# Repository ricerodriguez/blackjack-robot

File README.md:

# Blackjack Robot
Source code for a robot that automates a game of blackjack for 5 players.

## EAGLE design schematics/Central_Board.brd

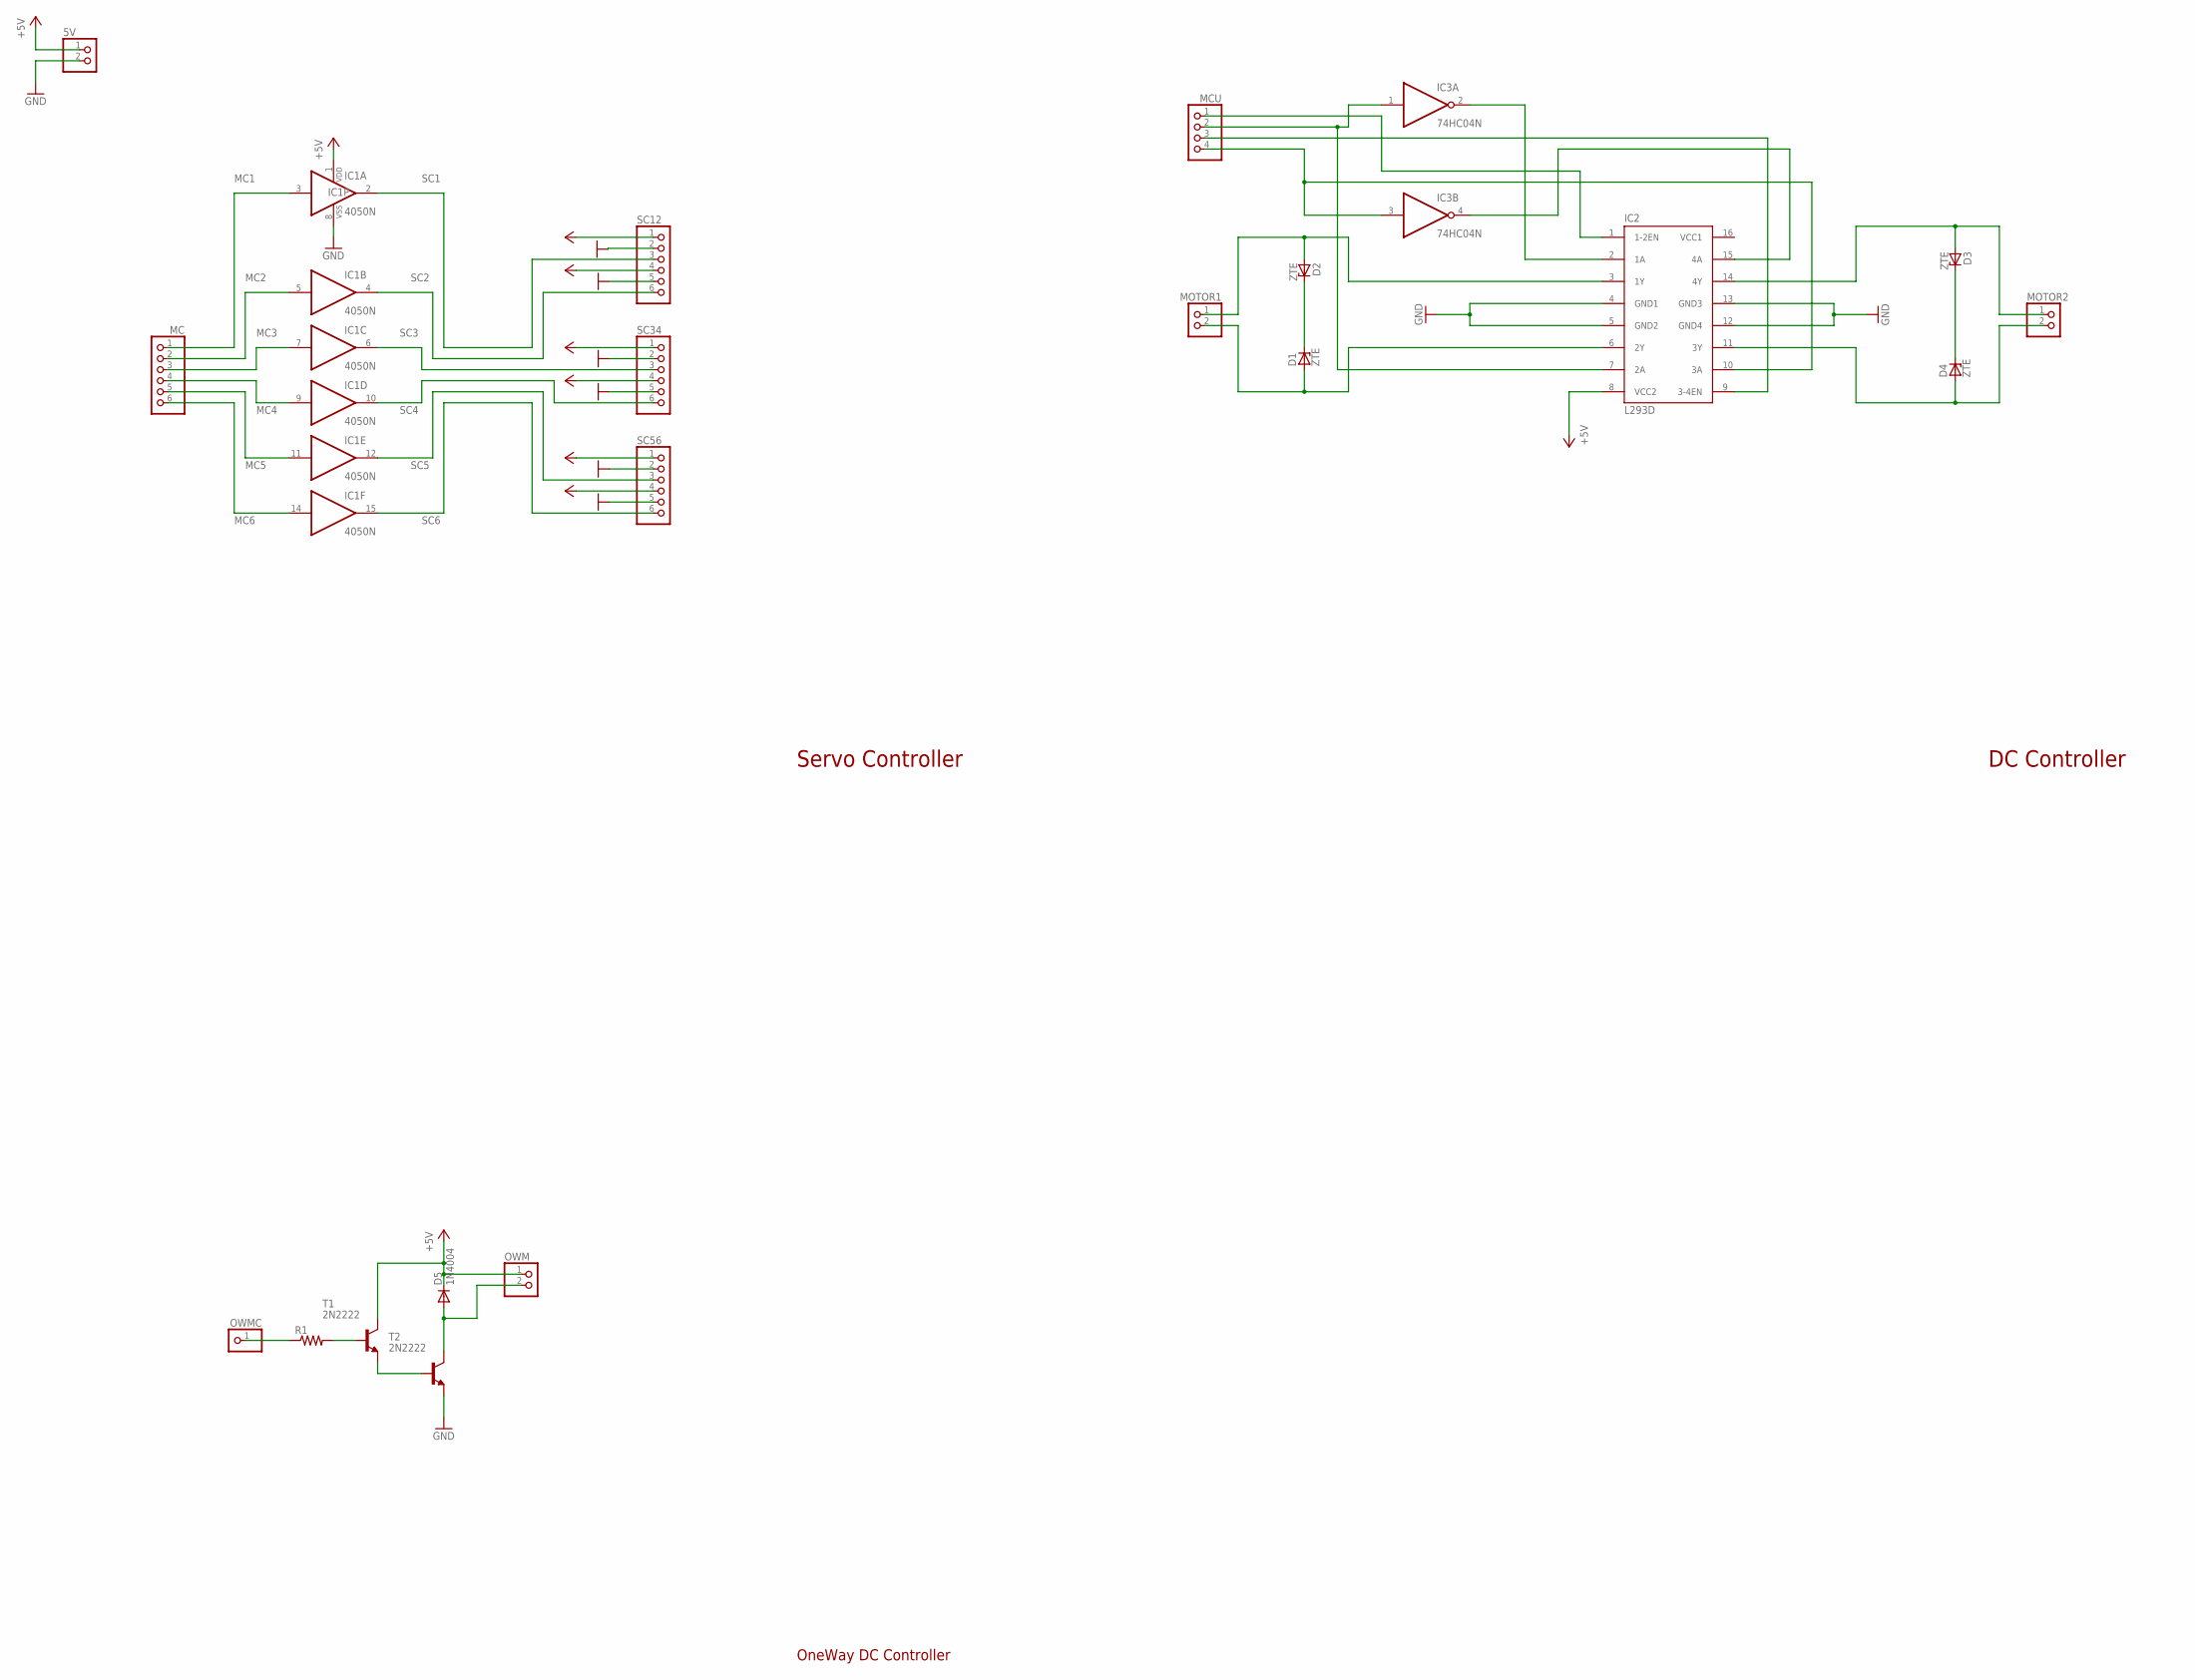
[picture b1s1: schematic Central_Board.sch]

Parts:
5V: PINHD-1X2; 1X02
D1, D2, D3, D4: ZTE; DO35Z10
D5: 1N4004; DO41-10
IC1: 4050N; DIL16
IC2: L293D; DIL16
IC3: 74HC04N; DIL14
MC: PINHD-1X6; 1X06
MCU: PINHD-1X4; 1X04
MOTOR1, MOTOR2: PINHD-1X2; 1X02
OWM: PINHD-1X2; 1X02
OWMC: PINHD-1X1; 1X01
R1: R-US_0207/10; 0207/10
SC12, SC34, SC56: PINHD-1X6; 1X06
T1, T2: 2N2222; TO92-ECB

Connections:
+5V: 5V.1, D5.C, IC1.1 (VDD), IC2.8 (VCC2), OWM.1, SC12.1, SC12.4, SC34.1, SC34.4, SC56.1, SC56.4, T1.C
GND: 5V.2, IC1.8 (VSS), IC2.4 (GND1), IC2.5 (GND2), IC2.12 (GND4), IC2.13 (GND3), IC3.7 (GND), SC12.2, SC12.5, SC34.2, SC34.5, SC56.2, SC56.5, T2.E
MC1: IC1.3 (I), MC.1
MC2: IC1.5 (I), MC.2
MC3: IC1.7 (I), MC.3
MC4: IC1.9 (I), MC.4
MC5: IC1.11 (I), MC.5
MC6: IC1.14 (I), MC.6
unnamed: D3.C, D4.C
unnamed: D3.A, IC2.14 (4Y), MOTOR2.1
unnamed: D4.A, IC2.11 (3Y), MOTOR2.2
unnamed: D2.A, IC2.3 (1Y), MOTOR1.1
unnamed: D1.A, IC2.6 (2Y), MOTOR1.2
unnamed: D1.C, D2.C
unnamed: IC2.2 (1A), IC3.2 (O)
unnamed: D5.A, OWM.2, T2.C
unnamed: R1.2, T1.B
unnamed: IC2.15 (4A), IC3.4 (O)
unnamed: IC2.7 (2A), IC3.1 (I), MCU.2
unnamed: IC2.10 (3A), IC3.3 (I), MCU.4
unnamed: IC2.1 (1-2EN), MCU.1
unnamed: IC2.9 (3-4EN), MCU.3
unnamed: OWMC.1, R1.1
unnamed: T1.E, T2.B
SC1: IC1.2 (O), SC12.3
SC2: IC1.4 (O), SC12.6
SC3: IC1.6 (O), SC34.3
SC4: IC1.10 (O), SC34.6
SC5: IC1.12 (O), SC56.3
SC6: IC1.15 (O), SC56.6
VCC: IC3.14 (VCC)
VCC1: IC2.16 (VCC1)

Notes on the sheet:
Servo Controller
DC Controller
OneWay DC Controller

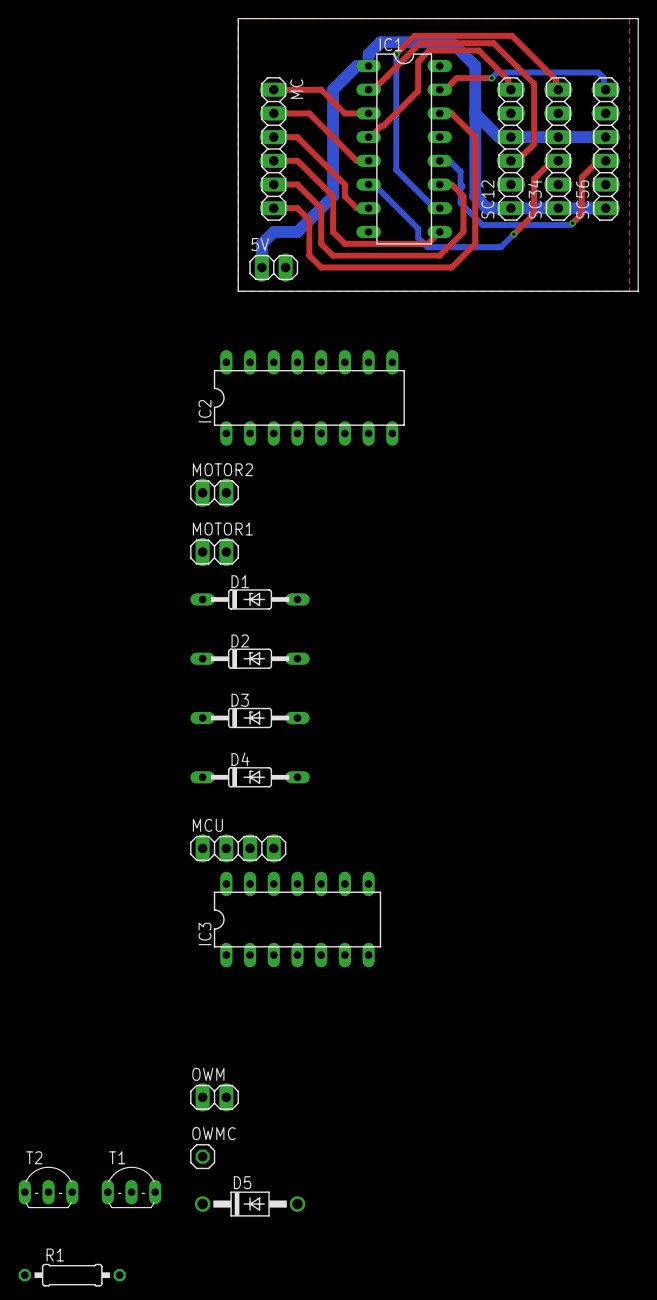
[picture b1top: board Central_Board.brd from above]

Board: 2 copper layers, 42.9 x 29.2 mm, 21 parts (0 on the bottom side), 30 nets.

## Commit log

2019-02-12 Test
2019-02-12 Commit tiny bit of code before trying test code from tutorial
2019-02-12 Look at differences in thresholded images
2019-02-12 Display images
2019-02-17 Lots of updates to gui
2019-02-17 Changes to GUI
2019-02-17 Fixed main window not showing up
2019-02-18 Added some fresh beats from soundimage dot org
2019-02-18 Removed unnecessary file
2019-02-18 Cleaned up code
2019-02-19 Minor improvements
2019-02-19 File structure
2019-02-19 Added more resources and placeholder
2019-02-26 Making changes to how cards stack
2019-02-27 Card display works with up to 6 cards
2019-03-10 Added test code and updated macros
2019-03-11 Added file extension to image file name
2019-03-11 fixed threading issues|
2019-03-11 Fixed issue of skipping over cards
2019-03-11 Added image cropping and test code for it to check algorithm
2019-03-15 adjusted autocropping
2019-03-20 Create central_board
2019-03-20 Create data
2019-03-20 Create inet_dsheets
2019-03-20 Added busted
2019-03-22 Change to test algorithm
2019-03-22 Fixed a stupid typo
2019-03-22 upload test images
2019-03-22 new image
2019-03-23 update pic
2019-03-23 again
2019-03-23 focused
2019-03-23 support
2019-03-23 Changes to test algorithm
2019-03-23 Fixed changes
2019-03-23 Trying to display the damn thing
2019-03-23 Whoopsies
2019-03-23 Added wait key
2019-03-23 fixes
2019-03-23 draw contours
2019-03-23 minor change
2019-03-23 Crop to contour
2019-03-26 tests
2019-03-26 fixed indent
2019-03-26 Change to see all contours
2019-03-26 Back to the one
2019-03-26 Actual image
2019-03-26 Boxes
2019-03-26 Trying
2019-03-26 Just trying to see anything
2019-03-26 Changed back
2019-04-09 Added new test algorithm
2019-04-10 Added attempt at rotating
2019-04-13 adding changes
2019-04-13 Major changes to test algorithm script, about to be tested
2019-04-13 pushing before i ruin something
2019-04-13 got it to find rank and suit
2019-04-13 Tried to streamline process
2019-04-13 can reliably find rank and suit
2019-04-13 Added print statement for rank, suit
2019-04-13 pushing before working without ssh
2019-04-13 Trying to add bounding boxes
2019-04-13 about to add the other half of find box
2019-04-13 Added second half
2019-04-14 about to optimize alg
2019-04-14 Broke up while loop into sequence of while loops
2019-04-14 Rotated and cropped to rank
2019-04-14 Changed boundaries to work for 3 of clubs
2019-04-14 about to optimize some more, saving first
2019-04-14 cropped and rotated to suit rank
2019-04-14 Creates new image for card with rank,suit
2019-04-16 More clean up, saved image to file
2019-04-16 fixed a couple minor issues
2019-04-16 Shortened prep function, testing something new out
2019-04-16 Changed how it determines rank from suit
2019-04-23 changed to cv VideoCapture
2019-04-23 Added test
2019-04-23 tmptst now works with new camera
2019-04-23 Changed image processor
2019-05-02 Upload example
2019-05-03 Made changes to multithreading, about to test
2019-05-04 add changes to im processing
2019-05-04 Added a bunch of shit for the actual dealer, needs testing
2019-05-04 got cropped rotation to work
2019-05-04 ensures order of corners and crops correctly
2019-05-04 it still doesnt match
2019-05-04 added idle output when no cmd
2019-05-06 PUI state machine
    state machine that was a pain to debug but worked fully at the end
2019-05-07 Diagrams and pics
2019-05-07 WIki text
